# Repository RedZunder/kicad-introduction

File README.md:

# kicad-introduction
This repository stores all necessary files for the Introduction to Electronic Design 101 with KiCAD, on 2nd June 2026.

The file [jlpcb_rules](./jlpcb_rules/jlpcb_rules.kicad_pcb) contains the constraints given by JLPCB's manufacturing capabilities, as well as default trace and via sizes.

The trace sizes have been calculated using this [trace width calculator](https://nick.desmith.net/Electronics/TraceWidth.html).

The items in the [icons](./icons) folder contains free sample logos to add to the board, for testing. You can of course add your own.
[sample_code](./sample_code) contains an example code for the ATTINY85 to match the functionality of the PCB.

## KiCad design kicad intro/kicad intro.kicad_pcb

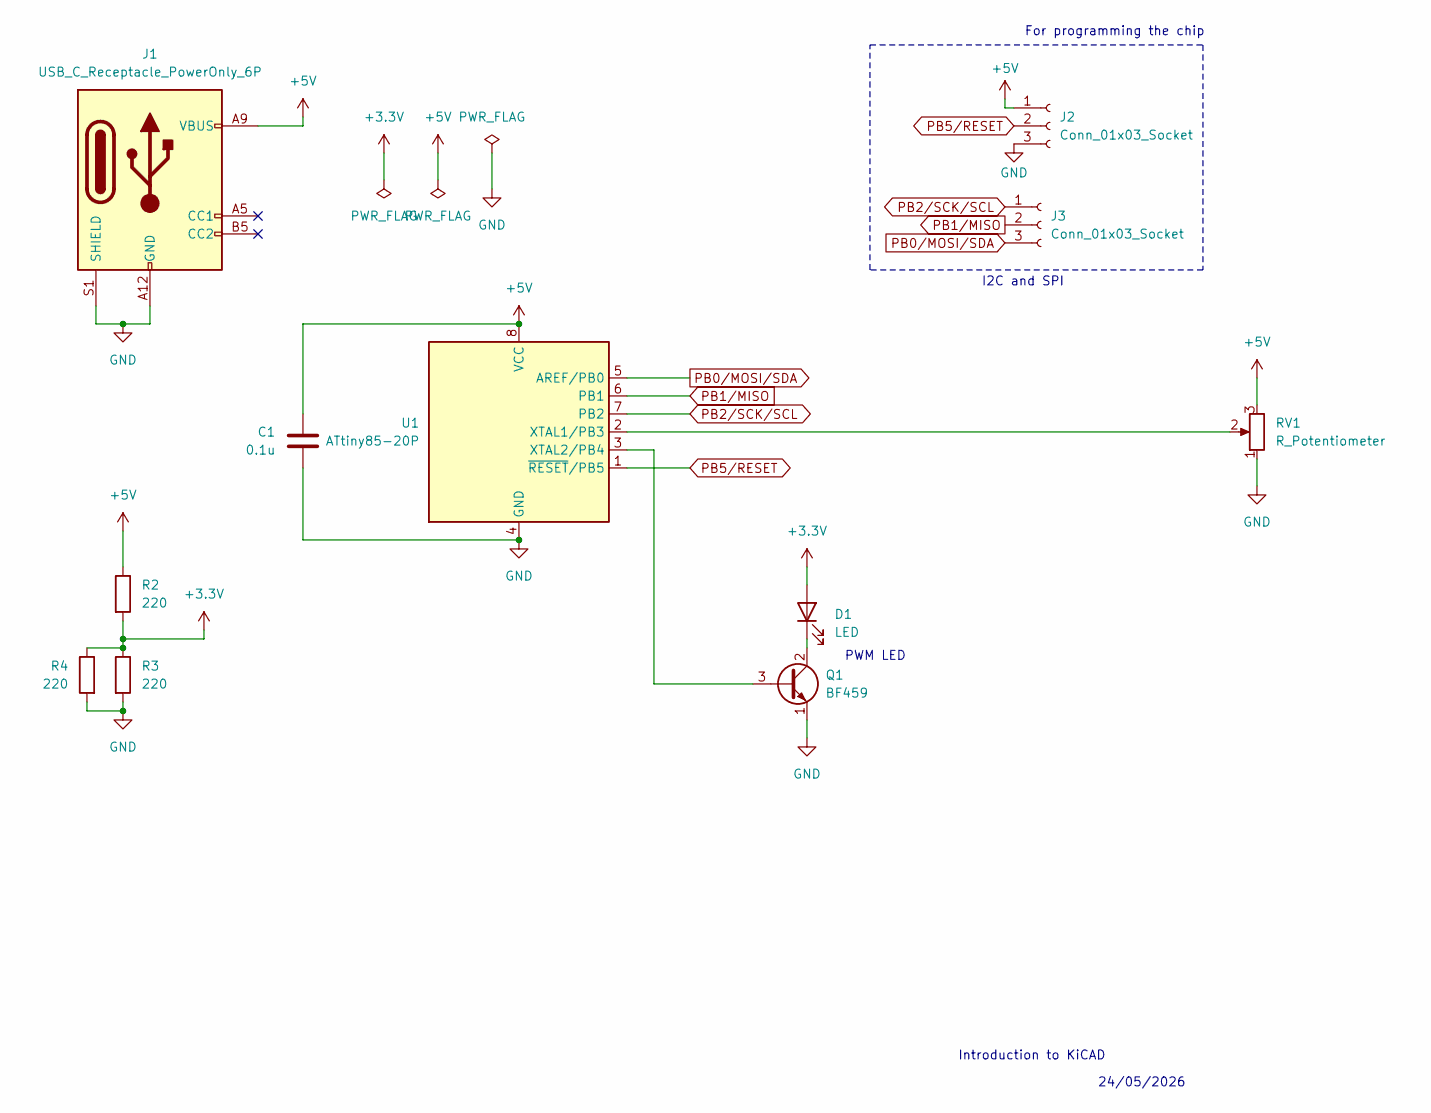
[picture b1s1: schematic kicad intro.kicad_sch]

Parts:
C1: 0.1u; C_Disc_D10.5mm_W5.0mm_P5.00mm
D1: LED; LED_D3.0mm
J1: USB_C_Receptacle_PowerOnly_6P; USB_C_Receptacle_GCT_USB4125-xx-x-0190_6P_TopMnt_Horizontal
J2, J3: Conn_01x03_Socket; PinSocket_1x03_P2.54mm_Vertical
Q1: BF459; TO-126-3_Vertical
R2, R3, R4: 220; R_Axial_DIN0207_L6.3mm_D2.5mm_P7.62mm_Horizontal
RV1: R_Potentiometer; Potentiometer_Bourns_3266Y_Vertical
U1: ATtiny85-20P; DIP-8_W7.62mm

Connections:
+3.3V: D1.2 (A), R2.2, R3.1, R4.1
+5V: C1.2, J1.A9 (VBUS), J1.B9 (VBUS), J2.1, R2.1, RV1.3, U1.8 (VCC)
GND: C1.1, J1.A12 (GND), J1.B12 (GND), J1.S1 (SHIELD), J2.3, Q1.1 (E), R3.2, R4.2, RV1.1, U1.4 (GND)
unnamed: D1.1 (K), Q1.2 (C)
unnamed: Q1.3 (B), U1.3 (XTAL2/PB4)
unnamed: RV1.2, U1.2 (XTAL1/PB3)
PB0/MOSI/SDA: J3.3, U1.5 (AREF/PB0)
PB1/MISO: J3.2, U1.6 (PB1)
PB2/SCK/SCL: J3.1, U1.7 (PB2)
PB5/RESET: J2.2, U1.1 (~RESET/PB5)

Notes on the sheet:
Introduction to KiCAD
PWM LED
24/05/2026
I2C and SPI
For programming the chip

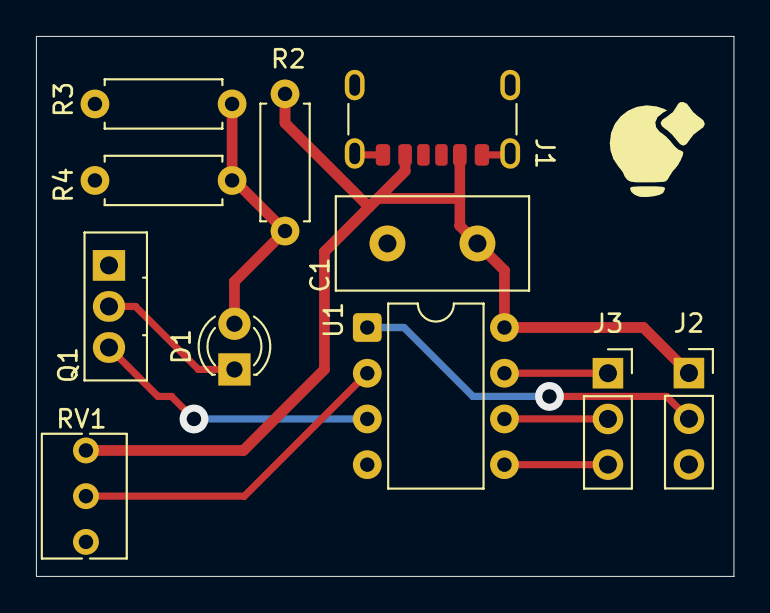
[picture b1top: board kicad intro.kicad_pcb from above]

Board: 2 copper layers, 38.8 x 30.0 mm, 11 parts (0 on the bottom side), 10 nets.

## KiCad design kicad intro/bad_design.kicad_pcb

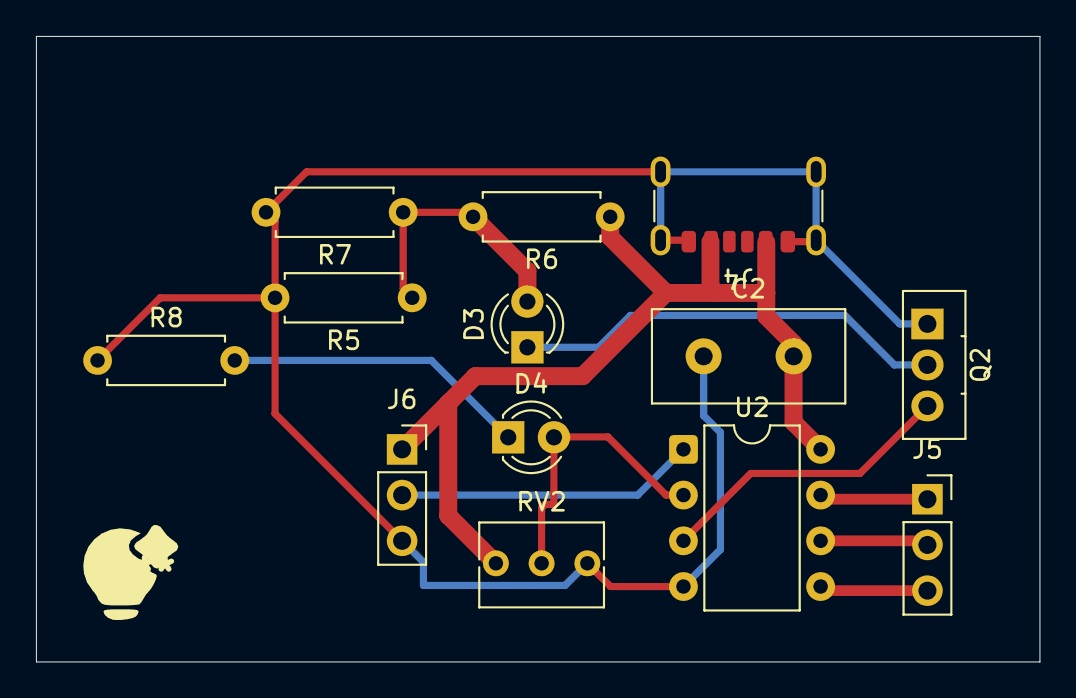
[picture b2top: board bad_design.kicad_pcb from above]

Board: 2 copper layers, 55.8 x 34.8 mm, 13 parts (0 on the bottom side), 11 nets.

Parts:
C2: 0.1u; C_Disc_D10.5mm_W5.0mm_P5.00mm
D3, D4: LED; LED_D3.0mm
J4: USB_C_Receptacle_PowerOnly_6P; USB_C_Receptacle_GCT_USB4125-xx-x-0190_6P_TopMnt_Horizontal
J5, J6: Conn_01x03_Socket; PinSocket_1x03_P2.54mm_Vertical
Q2: BF459; TO-126-3_Vertical
R5, R6, R7, R8: 220; R_Axial_DIN0207_L6.3mm_D2.5mm_P7.62mm_Horizontal
RV2: R_Potentiometer; Potentiometer_Bourns_3266Y_Vertical
U2: ATtiny85-20P; DIP-8_W7.62mm

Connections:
+3.3V: D3.2 (A), R5.1, R6.2, R7.1
+5V: C2.2, J4.A9 (VBUS), J4.B9 (VBUS), J6.1, R6.1, RV2.3, U2.8 (VCC)
GND: C2.1, J4.A12 (GND), J4.B12 (GND), J4.S1 (SHIELD), J6.3, Q2.1 (E), R5.2, R7.2, R8.1, RV2.1, U2.4 (GND)
unnamed: D3.1 (K), Q2.2 (C)
unnamed: D4.2 (A), RV2.2, U2.2 (XTAL1/PB3)
unnamed: D4.1 (K), R8.2
unnamed: J5.1, U2.7 (PB2)
unnamed: J5.2, U2.6 (PB1)
unnamed: J5.3, U2.5 (AREF/PB0)
unnamed: J6.2, U2.1 (~RESET/PB5)
unnamed: Q2.3 (B), U2.3 (XTAL2/PB4)

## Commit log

2026-05-23 Added original repo
2026-05-23 Linked properly to repo
2026-05-23 added open source icons
2026-05-27 Fixed rules
2026-05-28 finished PCB, updated README
2026-05-28 forgot the PCB
2026-05-28 added examples of bad design
2026-05-31 Separated ground pours
2026-06-02 Updated sample code and design
